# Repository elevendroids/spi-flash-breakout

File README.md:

# SPI NOR Flash ROM Breakout Board

Small breakout board for SPI NOR Flash ROM chips in SOP-8 package

# Features

- supports most standard NOR Flash chips in SOP-8 package
- standard 8-pin ISP header with bus termination resistors (if needed)
- pin headers exposing each signal for testing
- pull-up resistors for /CS, /WP and /HOLD signals
- optional pull-down for /WP signal

Designed in KiCad 5.1.7

Schematic: [PDF](docs/spi-flash-breakout.pdf)

License: [CC BY-SA 4.0](https://creativecommons.org/licenses/by-sa/4.0/)

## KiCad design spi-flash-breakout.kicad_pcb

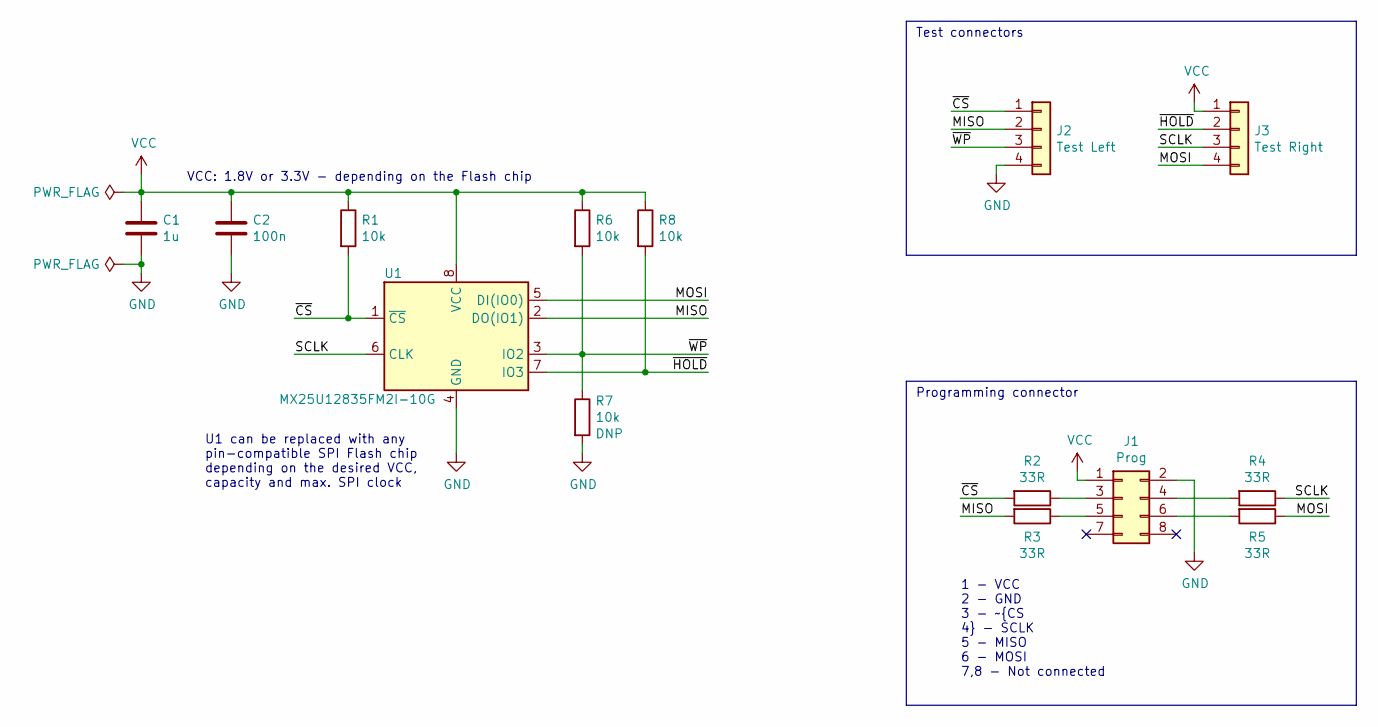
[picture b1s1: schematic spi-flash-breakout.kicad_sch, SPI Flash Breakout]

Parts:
C1: 1u; C_0603_1608Metric
C2: 100n; C_0603_1608Metric
J1: Prog; PinHeader_2x04_P2.54mm_Vertical
J2: Test Left; PinHeader_1x04_P2.54mm_Vertical
J3: Test Right; PinHeader_1x04_P2.54mm_Vertical
R1, R6, R7, R8: 10k; R_0603_1608Metric
R2, R3, R4, R5: 33R; R_0603_1608Metric
U1: MX25U12835FM2I-10G; SOIC-8_5.23x5.23mm_P1.27mm

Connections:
/MISO: J2.2, R3.2, U1.2 (DO(IO1))
/MOSI: J3.4, R5.1, U1.5 (DI(IO0))
/SCLK: J3.3, R4.1, U1.6 (CLK)
/~CS: J2.1, R1.2, R2.2, U1.1 (~CS)
/~HOLD: J3.2, R8.2, U1.7 (IO3)
/~WP: J2.3, R6.2, R7.1, U1.3 (IO2)
GND: C1.2, C2.2, J1.2, J2.4, R7.2, U1.4 (GND)
unnamed: J1.3, R2.1
unnamed: J1.4, R4.2
unnamed: J1.5, R3.1
unnamed: J1.6, R5.2
VCC: C1.1, C2.1, J1.1, J3.1, R1.1, R6.1, R8.1, U1.8 (VCC)

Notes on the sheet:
U1 can be replaced with any pin-compatible SPI Flash chip depending on the desired VCC, capacity and max. SPI clock
VCC: 1.8V or 3.3V - depending on the Flash chip
1 - VCC 2 - GND 3 - ~{CS 4} - SCLK 5 - MISO 6 - MOSI 7,8 - Not connected
Test connectors
Programming connector

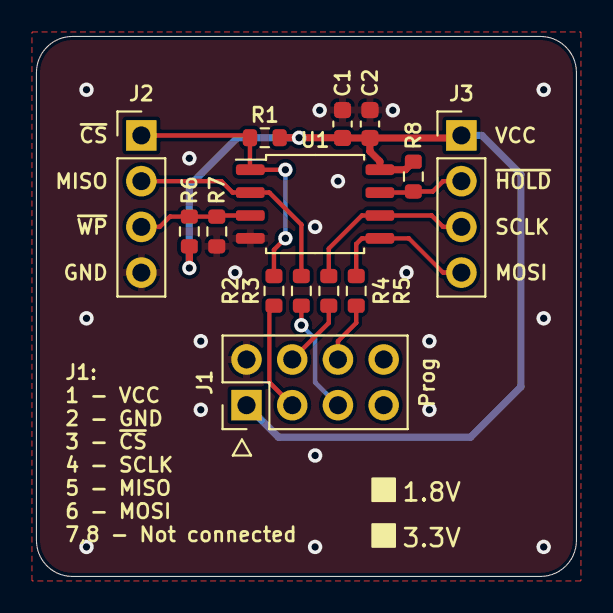
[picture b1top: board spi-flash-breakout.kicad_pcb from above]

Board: 2 copper layers, 30.0 x 30.0 mm, 14 parts (0 on the bottom side), 12 nets.

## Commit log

2020-10-27 Added README
2022-04-03 Project upgrade to KiCad 6

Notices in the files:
spi-flash-breakout.kicad_pcb:
(c) 2020 Michal Potrzebicz
CC BY-SA 4.0
